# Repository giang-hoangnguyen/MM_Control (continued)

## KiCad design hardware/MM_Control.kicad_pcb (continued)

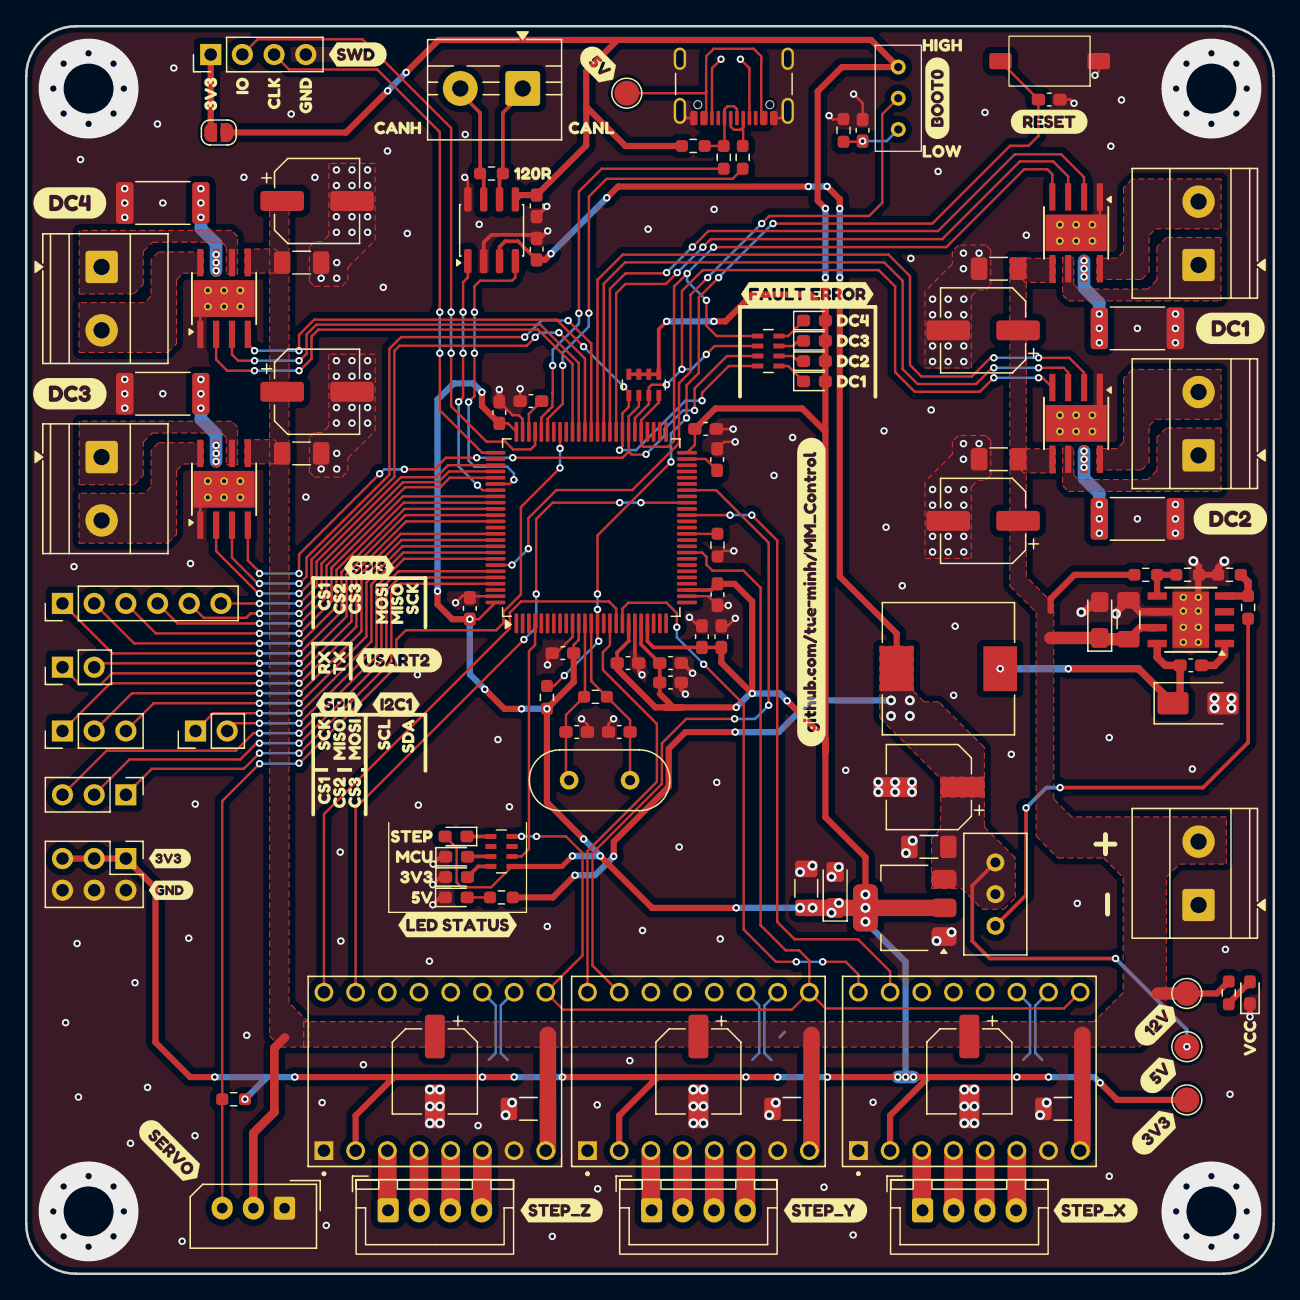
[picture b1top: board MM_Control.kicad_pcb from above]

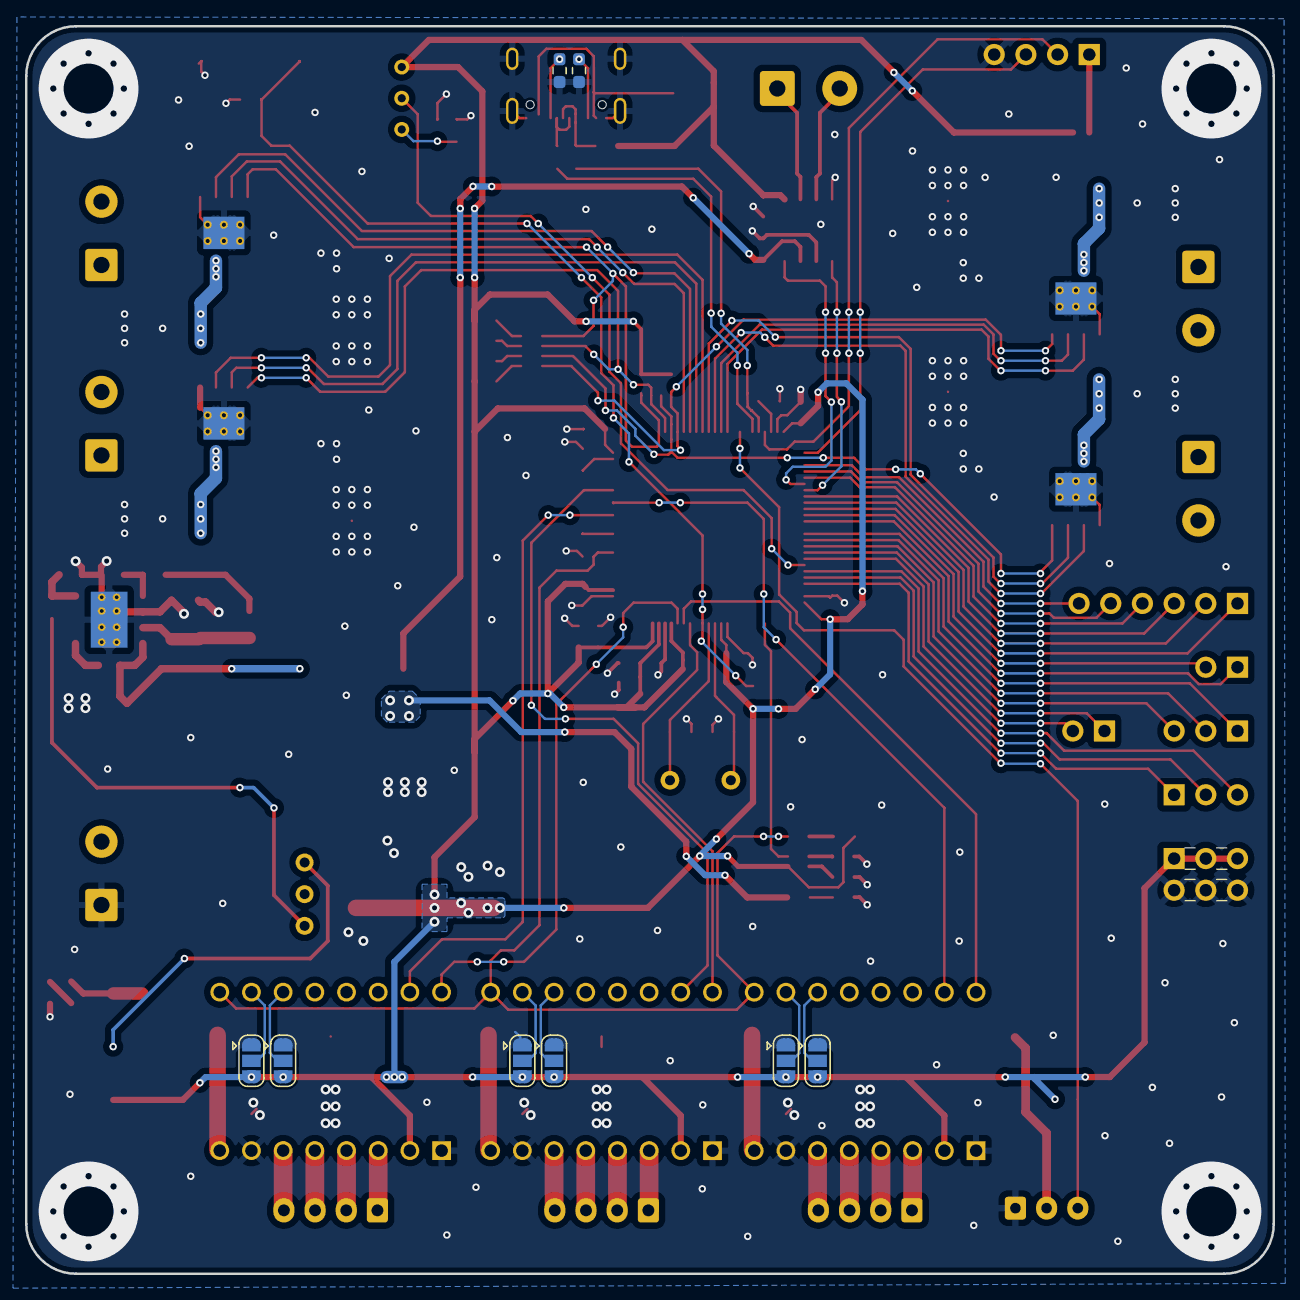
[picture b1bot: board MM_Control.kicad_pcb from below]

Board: 2 copper layers, 100.0 x 100.0 mm, 176 parts (8 on the bottom side), 107 nets.

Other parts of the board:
kibuzzard-6AAE0E6C: G***; kibuzzard-6AAE0E6C
kibuzzard-6AAE0ECB: G***; kibuzzard-6AAE0ECB
kibuzzard-6AAE0FD8: G***; kibuzzard-6AAE0FD8
kibuzzard-6AAE0FDE: G***; kibuzzard-6AAE0FDE
kibuzzard-6AAE0FE1: G***; kibuzzard-6AAE0FE1
kibuzzard-6AAE0FE6: G***; kibuzzard-6AAE0FE6
kibuzzard-6AAE10A6: G***; kibuzzard-6AAE10A6
kibuzzard-6AAE11A1: G***; kibuzzard-6AAE11A1
kibuzzard-6AAE11BA: G***; kibuzzard-6AAE11BA
kibuzzard-6AAE11CA: G***; kibuzzard-6AAE11CA
kibuzzard-6AAE12C7: G***; kibuzzard-6AAE12C7
kibuzzard-6AAE12D7: G***; kibuzzard-6AAE12D7
kibuzzard-6AAE12FE: G***; kibuzzard-6AAE12FE
kibuzzard-6AAE70A5: G***; kibuzzard-6AAE70A5
kibuzzard-6AAE70C3: G***; kibuzzard-6AAE70C3
kibuzzard-6AAE72CB: G***; kibuzzard-6AAE72CB
kibuzzard-6AAE75E4: G***; kibuzzard-6AAE75E4
kibuzzard-6AAE75E6: G***; kibuzzard-6AAE75E6
kibuzzard-6AAE76A6: G***; kibuzzard-6AAE76A6
kibuzzard-6AAE76A8: G***; kibuzzard-6AAE76A8
kibuzzard-6AAE111B: G***; kibuzzard-6AAE111B
kibuzzard-6AAE131B: G***; kibuzzard-6AAE131B
kibuzzard-6AAE131F: G***; kibuzzard-6AAE131F
kibuzzard-6AAE137A: G***; kibuzzard-6AAE137A
kibuzzard-6AAE137D: G***; kibuzzard-6AAE137D
kibuzzard-6AAE712B, kibuzzard-6AAE712B#2: G***; kibuzzard-6AAE712B
kibuzzard-6AAE746A, kibuzzard-6AAE746A#2: G***; kibuzzard-6AAE746A
kibuzzard-6AAE747C, kibuzzard-6AAE747C#2: G***; kibuzzard-6AAE747C
kibuzzard-6AAE748A: G***; kibuzzard-6AAE748A
kibuzzard-6AAE1091: G***; kibuzzard-6AAE1091
kibuzzard-6AAE1124: G***; kibuzzard-6AAE1124
kibuzzard-6AAE1171: G***; kibuzzard-6AAE1171
kibuzzard-6AAE1324: G***; kibuzzard-6AAE1324
kibuzzard-6AAE1368: G***; kibuzzard-6AAE1368
kibuzzard-6AAE1376: G***; kibuzzard-6AAE1376
kibuzzard-6AAE7140: G***; kibuzzard-6AAE7140
kibuzzard-6AAE7148: G***; kibuzzard-6AAE7148
kibuzzard-6AAE7310: G***; kibuzzard-6AAE7310
kibuzzard-6AAE7386: G***; kibuzzard-6AAE7386
kibuzzard-6AAE7481, kibuzzard-6AAE7481#2: G***; kibuzzard-6AAE7481
kibuzzard-6AAE7487: G***; kibuzzard-6AAE7487
kibuzzard-6AAE7490: G***; kibuzzard-6AAE7490
kibuzzard-6AAE7606: G***; kibuzzard-6AAE7606
kibuzzard-6AAE7616: G***; kibuzzard-6AAE7616
kibuzzard-6AAEAE3A: G***; kibuzzard-6AAEAE3A
kibuzzard-6AAEAE3F: G***; kibuzzard-6AAEAE3F
kibuzzard-6AAEAE35: G***; kibuzzard-6AAEAE35
kibuzzard-6AAEAE99: G***; kibuzzard-6AAEAE99
kibuzzard-6AAEAF4A: G***; kibuzzard-6AAEAF4A
kibuzzard-6AAEB0A5: G***; kibuzzard-6AAEB0A5
kibuzzard-6AAEB0A9: G***; kibuzzard-6AAEB0A9
kibuzzard-6AAEB0D3: G***; kibuzzard-6AAEB0D3
kibuzzard-6AAEB075: G***; kibuzzard-6AAEB075
kibuzzard-6AAF97A4: G***; kibuzzard-6AAF97A4

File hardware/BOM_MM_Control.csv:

Nhóm,Ký hiệu (Reference),Số lượng,Giá trị / mã linh kiện,Kiểu chân (footprint),Ghi chú mua hàng và hàn
IC,U5,1,STM32F407VET6,"LQFP-100 14x14 mm, bước chân 0,5 mm","MCU. Khó hàn tay nhất: cần mỏ hàn mũi nhỏ + flux, hoặc nhờ xưởng"
IC,"U1,U3,U4,U6",4,DRV8872DDA,HTSOP-8 có pad nhiệt phía dưới,Driver động cơ DC. Pad nhiệt nằm dưới thân chip: cần hot-air hoặc lò reflow + kem hàn
IC,U12,1,TPS5430DDA,SO-PowerPAD-8,Buck VM → 5 V. Pad nhiệt phía dưới như DRV8872
IC,U2,1,AMS1117-3.3,SOT-223,"LDO 5 V → 3,3 V"
IC,U13,1,TJA1051T/3,SOIC-8,Transceiver CAN (ghi trong schematic: TJA1051T-3)
Module,"U7,U8,U9",3,TMC2209 SilentStepStick (V1.x),"Module 16 chân 2,54 mm (footprint tue_TMC2209)",Mua module có sẵn tản nhiệt; cắm vào đầu cái (header 1x8 x2 mỗi module) hoặc hàn thẳng. Kiểm tra sơ đồ chân module khớp footprint trước khi hàn
Nguồn,D2,1,SS34,SMA (DO-214AC),Diode schottky của buck
Nguồn,L2,1,22 µH,"SMD 10,4 x 10,4 x 4,8 mm",Cuộn cảm buck. Chọn dòng bão hòa >= 3 A (tải buck tối đa 3 A theo datasheet TPS5430)
Nguồn,RV1,1,"20 kΩ, Bourns 3296W","THT, núm vặn đứng",Chỉnh điện áp +5 V của buck. Xem hướng dẫn chỉnh trong tài liệu
Tinh thể,Y1,1,8 MHz,"HC49-4H, THT","Kèm C17, C18 = 10 pF"
Tụ,C1,1,220 µF,"Điện phân SMD 6,3 x 7,7 mm",Trên rail +5 V (đầu ra buck): điện áp định mức >= 10 V
Tụ,"C8,C9,C11,C13,C30,C31,C32",7,100 µF,"Điện phân SMD 6,3 x 5,9 mm","Trên rail VM (driver DC, driver bước). Điện áp định mức không ghi; footprint 6,3 mm giới hạn dải điện áp có sẵn, kiểm tra catalog khi chọn"
Tụ,C6,1,10 µF,Tantalum case A (EIA-3216-18),"Trên rail VM (đầu vào buck): điện áp định mức >= 1,5 x VM, nên chọn tụ gốm/tantalum >= 25 V nếu VM = 12 V. Chú ý cực tính tantalum. Schematic không ghi điện áp"
Tụ,C2,1,10 µF,Tantalum case A (EIA-3216-18),"Trên rail +3,3 V: điện áp định mức >= 6,3 V (chọn 10 V). Chú ý cực tính"
Tụ,"C5,C7,C10,C12,C34,C39,C40,C41",8,100 nF,1206,Trên rail VM: điện áp định mức >= 50 V
Tụ,"C4,C43",2,100 nF,1206,"Trên rail +3,3 V (C4) và +5 V (C43): >= 16 V"
Tụ,"C15,C16,C20,C21,C22,C23,C24,C25,C26,C27,C36,C38",12,100 nF,0603,Tụ lọc nguồn MCU và chân NRST
Tụ,"C28,C29",2,1 µF,0603,
Tụ,"C14,C19",2,"2,2 µF",0603,"Nối vào chân VCAP_1 và VCAP_2 của STM32, theo datasheet MCU thường dùng 2,2 µF"
Tụ,"C17,C18",2,10 pF,0603,Tải thạch anh
Tụ,C37,1,10 nF,0603,Bootstrap buck
Điện trở,"R2,R3,R4,R20",4,"0,2 Ω",2512,"Điện trở cảm biến dòng ISEN của DRV8872. Ngưỡng giới hạn dòng tính ~1,75 A mỗi kênh (0,35 V / 0,2 Ω theo datasheet DRV8872)"
Điện trở,"R6,R8,R11",3,10 kΩ,0603,
Điện trở,"R1,R7",2,100 kΩ,0603,
Điện trở,R5,1,1 MΩ,0603,Song song thạch anh
Điện trở,R27,1,"4,7 kΩ",0603,Chia áp hồi tiếp buck
Điện trở,R18,1,12 kΩ,0603,Chia áp hồi tiếp buck (nối RV1)
Điện trở,R15,1,43 kΩ,0603,Chia áp chân EN của buck (cùng R1)
Điện trở,"R9,R10",2,"5,1 kΩ",0603,CC1/CC2 của USB-C
Điện trở,R12,1,"1,5 kΩ",0603,Kéo lên D+ (USB full-speed)
Điện trở,"R13,R14",2,22 Ω,0603,Nối tiếp D+/D-
Điện trở,R17,1,680 Ω (ghi 681),0603,LED 5V1
Điện trở,R23,1,1 kΩ (ghi 102),0603,LED VCC1
Điện trở,R21,1,120 Ω,0603,Điện trở kết cuối CAN
Điện trở,"RN1,RN2,RN3",3,"470 Ω (ghi 471), mảng 4 điện trở",R_Array_Concave_4x0603,Điện trở hạn dòng cho các LED còn lại
LED,"DC_Fault1-4, MCU1, STEP_EN1, 3V3, 5V1, VCC1",9,LED,0603,"Màu LED không quy định trong schematic; chọn tùy ý (gợi ý: lỗi = đỏ, nguồn = xanh)"
Kết nối,"J8, J7, J23, J24, J25",5,"Terminal vít 5,08 mm 2 cực (Phoenix MKDS 1,5/2-5,08)","THT, cắm ngang","J8 = nguồn vào; J7, J23, J24, J25 = DC1…DC4"
Kết nối,J17,1,"Terminal vít 5,0 mm 2 cực (MaiXu MX126-5.0-02P)",THT,"CAN_L, CAN_H"
Kết nối,"J4,J5,J6",3,JST XH 4 chân B4B-XH-A,"THT, cắm đứng",Động cơ bước. Mua kèm dây/đầu XH 4P đối ứng
Kết nối,J1,1,Molex SPOX 5267-03A (3 chân),"THT, cắm đứng","Bus servo: GND, VM1, tín hiệu. Mua kèm đầu cắm SPOX đối ứng"
Kết nối,J22,1,USB-C GCT USB4105-xx-A (16 chân),"SMD, cắm ngang","Cổng USB (dữ liệu, không cấp nguồn cho board)"
Kết nối,J2,1,"Header 1x6, 2,54 mm",THT,"SPI3: CS1-3, MOSI, MISO, SCK"
Kết nối,J3,1,"Header 1x4, 2,54 mm",THT,"SWD: 3V3 (qua jumper swd-3v3), SWDIO, SWCLK, GND"
Kết nối,"J9,J10",2,"Header 1x2, 2,54 mm",THT,"J9 = I2C (SCL, SDA); J10 = UART (RX, TX)"
Kết nối,"J11,J12",2,"Header 1x3, 2,54 mm",THT,"SPI1: J11 = SCK, MISO, MOSI; J12 = CS3, CS2, CS1"
Kết nối,J18,1,"Header 2x3, 2,54 mm",THT,Cổng cấp 3V3 và GND cho module ngoài
Nút/công tắc,SW1,1,"Nút nhấn RESET SMD 3 x 6 x 2,5 mm",SMD,Footprint tue_sw_smd_3x6x2.5mm
Nút/công tắc,SW3,1,"Công tắc gạt SPDT SS12D00 (chân 2,5 mm, 3P)",SMD,Chọn BOOT0 (LOW = chạy chương trình)
Jumper hàn,"MS1.1-1.3, MS2.1-2.3",6,Jumper hàn 3 pad (không có linh kiện),SolderJumper-3,"Chọn vi bước cho từng TMC2209: phải hàn nối một phía, không để hở"
Jumper hàn,swd-3v3,1,Jumper hàn 2 pad (không có linh kiện),SolderJumper-2,Mặc định hở. Chỉ hàn nối khi muốn cấp 3V3 từ bộ nạp qua J3
Cơ khí,4 lỗ góc,4,Vít M4,"Lỗ Ø4,2 tại (±45, ±45) mm",Dùng cho vỏ in 3D (xem enclosure/)

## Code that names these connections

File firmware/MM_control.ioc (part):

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Mcu.Name=STM32F407V(E-G)Tx
Mcu.Package=LQFP100
Mcu.UserName=STM32F407VETx
PA11.Mode=Device_Only
PA11.Signal=USB_OTG_FS_DM
PA12.Mode=Device_Only
PA12.Signal=USB_OTG_FS_DP
PA13.Mode=Serial_Wire
PA13.Signal=SYS_JTMS-SWDIO
PA14.Mode=Serial_Wire
PA14.Signal=SYS_JTCK-SWCLK
PA9.GPIOParameters=GPIO_Label
PA9.GPIO_Label=SERVO_TX
PA9.Mode=Half_duplex(single_wire_mode)
PA9.Signal=USART1_TX
PB3.Mode=Full_Duplex_Master
PB3.Signal=SPI1_SCK
PB4.Mode=Full_Duplex_Master
PB4.Signal=SPI1_MISO
PB5.Mode=Full_Duplex_Master
PB5.Signal=SPI1_MOSI
PB6.Mode=I2C
PB6.Signal=I2C1_SCL
PB7.Mode=I2C
PB7.Signal=I2C1_SDA
PB8.GPIOParameters=GPIO_Label
PB8.GPIO_Label=SPI1_CS1
PB8.Signal=GPIO_Output
PB9.GPIOParameters=GPIO_Label
PB9.GPIO_Label=SPI1_CS2
PB9.Signal=GPIO_Output
PC0.GPIOParameters=GPIO_Label
PC0.GPIO_Label=STEP_DIR4
PC0.Signal=GPIO_Output
PC1.GPIOParameters=GPIO_Label
PC1.GPIO_Label=STEP_DIR3
PC1.Signal=GPIO_Output
PC10.Mode=Full_Duplex_Master
PC10.Signal=SPI3_SCK
PC11.Mode=Full_Duplex_Master
PC11.Signal=SPI3_MISO
PC12.Mode=Full_Duplex_Master
PC12.Signal=SPI3_MOSI
PC2.GPIOParameters=GPIO_Label
PC2.GPIO_Label=STEP_DIR2
PC2.Signal=GPIO_Output
PC3.GPIOParameters=GPIO_Label
PC3.GPIO_Label=STEP_DIR1
PC3.Signal=GPIO_Output
PC5.GPIOParameters=GPIO_Label
PC5.GPIO_Label=STEP_ENABLE
PC5.Signal=GPIO_Output
PC6.GPIOParameters=GPIO_Label
PC6.GPIO_Label=DC-31
PC6.Signal=S_TIM3_CH1
PC7.GPIOParameters=GPIO_Label
PC7.GPIO_Label=DC_32
PC7.Signal=S_TIM3_CH2
PC8.GPIOParameters=GPIO_Label
PC8.GPIO_Label=DC_41
PC8.Signal=S_TIM3_CH3
PC9.GPIOParameters=GPIO_Label
PC9.GPIO_Label=DC_42
PC9.Signal=S_TIM3_CH4
PD0.Mode=CAN_Activate
PD0.Signal=CAN1_RX
PD1.Mode=CAN_Activate
PD1.Signal=CAN1_TX
PD10.GPIOParameters=GPIO_Label
PD10.GPIO_Label=DC_F3
PD10.Signal=GPIO_Input
PD11.GPIOParameters=GPIO_Label
PD11.GPIO_Label=DC_F4
PD11.Signal=GPIO_Input
PD12.GPIOParameters=GPIO_Label
PD12.GPIO_Label=DC_11
PD12.Signal=S_TIM4_CH1
PD13.GPIOParameters=GPIO_Label
PD13.GPIO_Label=DC_12
PD13.Signal=S_TIM4_CH2
PD14.GPIOParameters=GPIO_Label
PD14.GPIO_Label=DC_21
PD14.Signal=S_TIM4_CH3
PD15.GPIOParameters=GPIO_Label
PD15.GPIO_Label=DC_22
PD15.Signal=S_TIM4_CH4
PD2.GPIOParameters=GPIO_Label
PD2.GPIO_Label=SPI3_CS1
PD2.Signal=GPIO_Output
PD3.GPIOParameters=GPIO_Label
PD3.GPIO_Label=SPI3_CS2
PD3.Signal=GPIO_Output
PD4.GPIOParameters=GPIO_Label
PD4.GPIO_Label=SPI3_CS1
PD4.Signal=GPIO_Output
PD5.Mode=Asynchronous
PD5.Signal=USART2_TX
PD6.Mode=Asynchronous
PD6.Signal=USART2_RX
PD8.GPIOParameters=GPIO_Label
PD8.GPIO_Label=DC_F1
PD8.Signal=GPIO_Input
PD9.GPIOParameters=GPIO_Label
PD9.GPIO_Label=DC_F2
PD9.Signal=GPIO_Input
PE0.GPIOParameters=GPIO_Label
PE0.GPIO_Label=SPI1_CS3
PE0.Signal=GPIO_Output
PE11.GPIOParameters=GPIO_Label
PE11.GPIO_Label=STEP_2
PE11.Signal=S_TIM1_CH2
PE13.GPIOParameters=GPIO_Label
PE13.GPIO_Label=STEP_3
PE13.Signal=S_TIM1_CH3
PE14.GPIOParameters=GPIO_Label
PE14.GPIO_Label=STEP_4
PE14.Signal=S_TIM1_CH4
PE5.GPIOParameters=GPIO_Label
PE5.GPIO_Label=LED_MCU
PE5.Signal=GPIO_Output
PE9.GPIOParameters=GPIO_Label
PE9.GPIO_Label=STEP_1
PE9.Signal=S_TIM1_CH1
PH0-OSC_IN.Mode=HSE-External-Oscillator
PH0-OSC_IN.Signal=RCC_OSC_IN
PH1-OSC_OUT.Mode=HSE-External-Oscillator
PH1-OSC_OUT.Signal=RCC_OSC_OUT
RCC.HSE_VALUE=8000000
RCC.SYSCLKFreq_VALUE=168000000
RCC.SYSCLKSource=RCC_SYSCLKSOURCE_PLLCLK
board=custom
